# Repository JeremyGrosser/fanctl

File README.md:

[Schematic](https://github.com/JeremyGrosser/fanctl/raw/master/hw/fanctl.pdf)

This project was meant to demonstrate closed loop PID control of a 3-pin PC
fan. While the resulting board works, I learned that the tachometer pin on the
fan is connected to a hall effect sensor, powered by +12V. This means that you
cannot sense and control the fan's speed at the same time. I came to the
conclusion that you should spend a few more dollars on a 4-pin fan that has an
onboard MOSFET and a separate signal for PWM.

I'm providing the the code and board files here as they may still be
interesting or useful as a reference or teaching tool.

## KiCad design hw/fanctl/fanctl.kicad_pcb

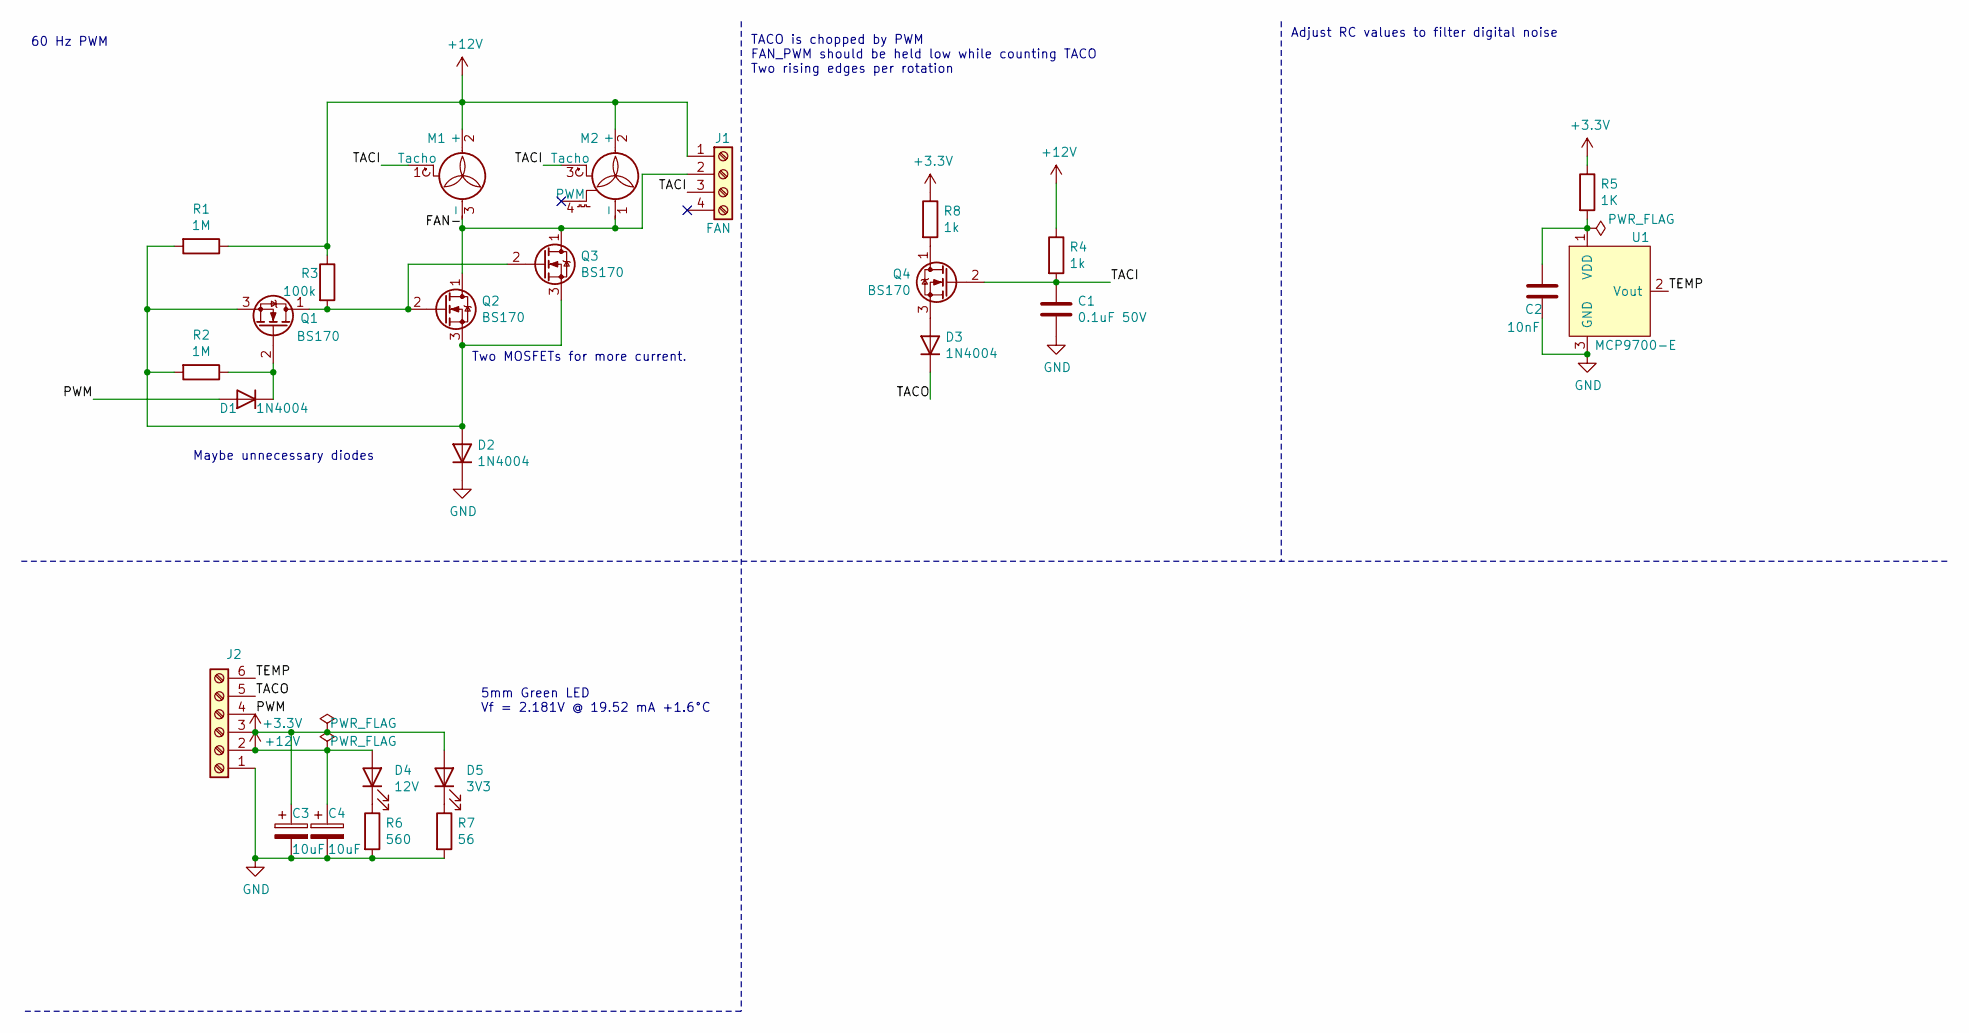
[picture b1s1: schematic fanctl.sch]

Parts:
C1: 0.1uF 50V; C_Disc_D4.7mm_W2.5mm_P5.00mm
C2: 10nF; C_Disc_D4.7mm_W2.5mm_P5.00mm
C3, C4: 10uF; CP_Radial_Tantal_D5.0mm_P2.50mm
D1, D2, D3: 1N4004; D_DO-41_SOD81_P10.16mm_Horizontal
D4: 12V; LED_D5.0mm
D5: 3V3; LED_D5.0mm
J1: FAN; TerminalBlock_bornier-4_P5.08mm
J2: Screw_Terminal_01x06; TerminalBlock_bornier-6_P5.08mm
M1: FAN; Molex_KK-254_AE-6410-03A_1x03_P2.54mm_Vertical
M2: FAN; Molex_KK-254_AE-6410-04A_1x04_P2.54mm_Vertical
Q1, Q2, Q3, Q4: BS170; TO-92_Inline
R1, R2: 1M; R_Axial_DIN0207_L6.3mm_D2.5mm_P7.62mm_Horizontal
R3: 100k; R_Axial_DIN0207_L6.3mm_D2.5mm_P7.62mm_Horizontal
R4, R8: 1k; R_Axial_DIN0207_L6.3mm_D2.5mm_P7.62mm_Horizontal
R5: 1K; R_Axial_DIN0207_L6.3mm_D2.5mm_P7.62mm_Horizontal
R6: 560; R_Axial_DIN0207_L6.3mm_D2.5mm_P7.62mm_Horizontal
R7: 56; R_Axial_DIN0207_L6.3mm_D2.5mm_P7.62mm_Horizontal
U1: MCP9700-E; TO-92_Inline

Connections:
+3V3: C3.1, D5.2 (A), J2.3, R5.1, R8.1
+12V: C4.1, D4.2 (A), J1.1, J2.2, M1.2 (+), M2.2 (+), R1.1, R3.1, R4.1
/FAN-: J1.2, M1.3 (-), M2.1 (-), Q2.1 (D), Q3.1 (D)
/PWM: D1.2 (A), J2.4
/TACI: C1.1, J1.3, M1.1 (Tacho), M2.3 (Tacho), Q4.2 (G), R4.2
/TACO: D3.1 (K), J2.5
/TEMP: J2.6, U1.2 (Vout)
GND: C1.2, C2.2, C3.2, C4.2, D2.1 (K), J2.1, R6.2, R7.2, U1.3 (GND)
unnamed: C2.1, R5.2, U1.1 (VDD)
unnamed: D1.1 (K), Q1.2 (G), R2.1
unnamed: D2.2 (A), Q1.3 (S), Q2.3 (S), Q3.3 (S), R1.2, R2.2
unnamed: D3.2 (A), Q4.3 (S)
unnamed: D4.1 (K), R6.1
unnamed: D5.1 (K), R7.1
unnamed: Q1.1 (D), Q2.2 (G), Q3.2 (G), R3.2
unnamed: Q4.1 (D), R8.2

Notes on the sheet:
Two MOSFETs for more current.
60 Hz PWM
Maybe unnecessary diodes
TACO is chopped by PWM FAN_PWM should be held low while counting TACO Two rising edges per rotation
Adjust RC values to filter digital noise
5mm Green LED Vf = 2.181V @ 19.52 mA +1.6°C

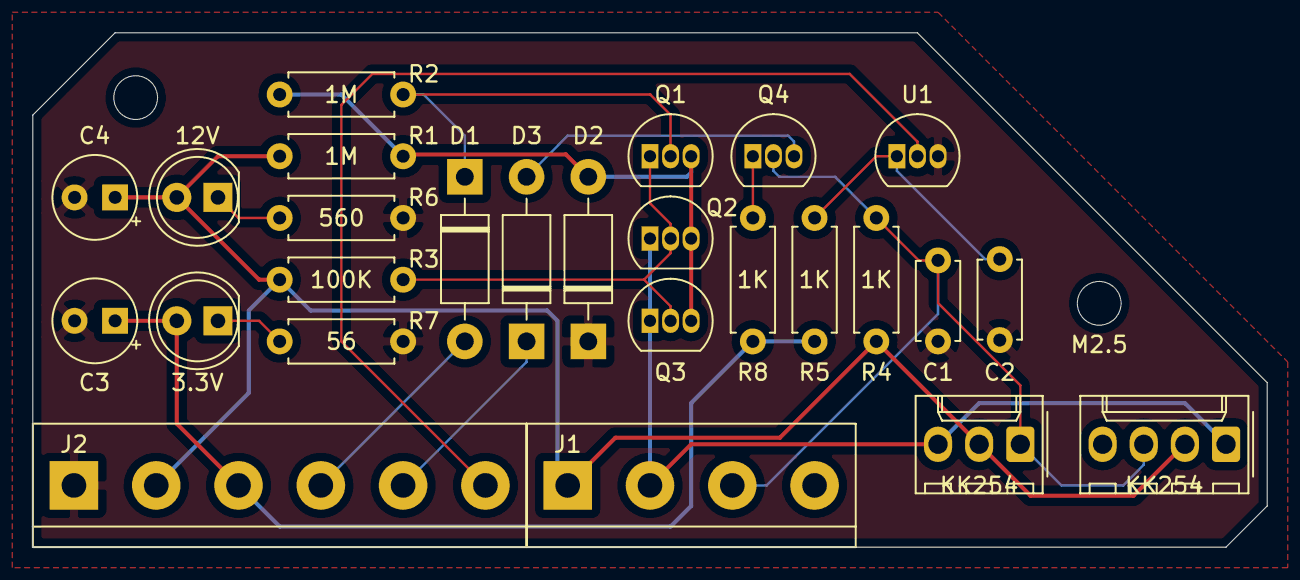
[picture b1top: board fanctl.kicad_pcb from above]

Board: 2 copper layers, 76.2 x 31.8 mm, 27 parts (0 on the bottom side), 16 nets.

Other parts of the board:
M2.5: MountingHole_2.7mm_M2.5_ISO14580

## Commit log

2020-02-23 self test
2020-02-24 all sensors read at once
2020-02-24 embedded build
2020-02-24 drivers!
2020-02-24 linker gc
2020-02-24 abstract platform and run simulated tests on native
2020-02-24 native is now called simulator
2020-02-24 more simulation
2020-02-26 null i2c port
2020-03-04 Major refactor
2020-03-04 fan with pwm mosfet works
2020-03-04 get rpm tests
2020-03-04 untested temperature sensor ADC
2020-03-04 nuke submodule
2020-03-05 pid control
2020-03-07 Release 1
2021-07-06 schematic drc
2021-07-06 footprints
2021-07-06 pcb layout
2021-07-06 layout done
2021-07-06 schematic and silkscreen nits
2021-07-06 resize schematic for US Letter and generate PDF
2021-07-06 renders
2021-07-09 controller
2021-07-11 fan servo
2021-07-11 style mostly
2021-07-11 tilde depend
2021-07-16 pid control sim
2021-07-16 pid tuning
2021-07-24 move platform specific code out of generic_pid_control
2021-07-24 remove sim
2021-07-24 pure
2021-07-25 reasonably good enough
2021-07-25 no averaging
2021-07-25 shell
2021-07-25 quiet
2021-07-25 style
2022-08-31 kicad 5.1
2022-08-31 README and LICENSE
2022-08-31 add pcb render to readme
2022-08-31 crop pcb image
2022-08-31 Link to schematic
2022-08-31 link to raw pdf
